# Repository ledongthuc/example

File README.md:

# Where I write my guide 
*please use Ctrl + F5 or Command + F5 to search.*

## List guide:

+ [Bluetooth 4.0 with HM-10 module!](bluetooth-4-with-hm-10/)
+ [C Programming language!](c-programming-language/)
+ [C - Standard library](c-standard-library/)
+ [Design Pattern!](design-pattern/)
+ [Relay with Arduino!](relay/)

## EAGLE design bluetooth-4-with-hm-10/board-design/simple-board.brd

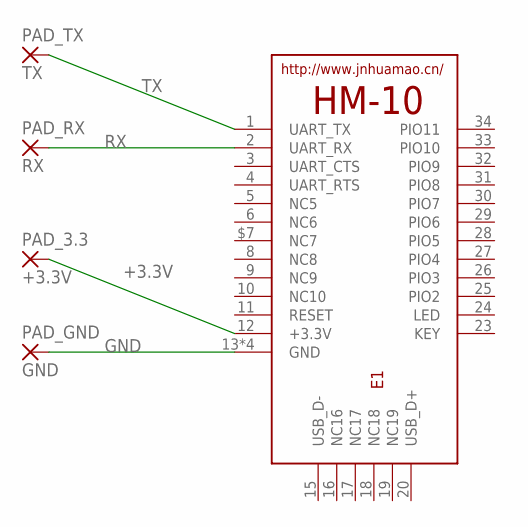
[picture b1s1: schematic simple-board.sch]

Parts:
E1: HM-10-BOARD; 26.9X13X2.2_BOARD
PAD_3.3: +3.3V; 1,6/0,8
PAD_GND: GND; 1,6/0,8
PAD_RX: RX; 1,6/0,8
PAD_TX: TX; 1,6/0,8

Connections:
+3.3V: E1.12 (+3.3V), PAD_3.3.1
GND: E1.13 (GND), E1.14 (GND), E1.21 (GND), E1.22 (GND), PAD_GND.1
RX: E1.2 (UART_RX), PAD_RX.1
TX: E1.1 (UART_TX), PAD_TX.1

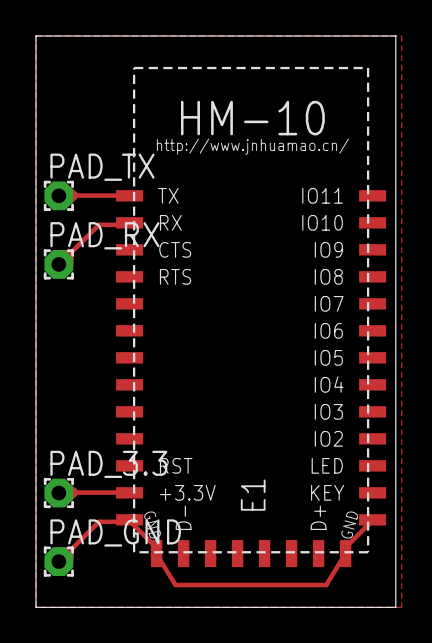
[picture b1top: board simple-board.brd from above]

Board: 2 copper layers, 20.0 x 31.7 mm, 5 parts (0 on the bottom side), 4 nets.

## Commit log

2015-04-19 Update: update list guide in README and add board's design of BLE HM-10
2015-04-19 Update: Move C programming language guide to this project
2015-04-19 Update: move content to this repository
2015-04-19 Update: move relay guide
2015-04-19 Update: remove useless file
2015-04-19 Update: readme file
2015-04-19 Rename README.rm to README.rd
2015-04-19 Rename README.rd to README.md
2015-04-19 Update: correct content of readme
2015-04-20 Update: planeground board
2015-04-20 Update: translate section relays connection
2015-04-21 Update: convert to english
2015-04-22 Update: full translate guide of relay component
2015-04-22 Update: resize image
2015-04-22 Update: correct grammar of readme in relay guide
2015-04-23 Update: replace 3 images with english
2015-04-25 New: some notes in readme file
2015-04-25 Update: some note in make
2015-04-26 Update: Add 3 example of make: simple, compact and super compact
2015-04-26 Update: change current README file
2015-04-26 Update: update README file
2015-04-26 Update: rename makefile to Makefile
2015-04-26 Update: example 4: makefile include another one
2015-04-26 Update: twin Makefile
2015-04-26 Update: update content of source 4 and source5, update text in README (example 3,4,5)
2015-06-13 Update: move to src2
2015-06-16 Update: rename src2 to src
2015-06-16 Update: example for library assert.h
2015-06-16 Update: move source file to src folder
2015-06-16 Update: describe about assert.h library
